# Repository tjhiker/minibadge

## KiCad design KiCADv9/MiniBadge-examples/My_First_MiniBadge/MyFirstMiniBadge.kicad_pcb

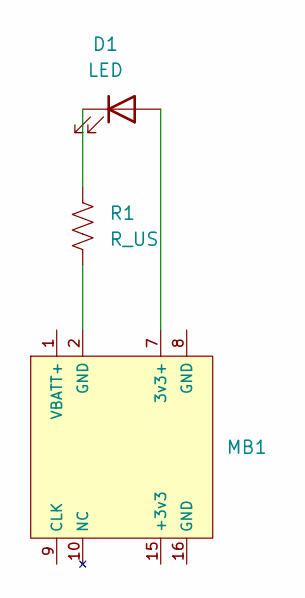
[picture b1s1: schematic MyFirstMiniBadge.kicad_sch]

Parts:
D1: LED; LED_1206_3216Metric_Pad1.42x1.75mm_HandSolder
MB1: MiniBadge_Simple_Edge_Curved
R1: R_US; R_1206_3216Metric_Pad1.30x1.75mm_HandSolder

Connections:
unnamed: D1.2 (A), MB1.7 (3v3+)
unnamed: D1.1 (K), R1.1
unnamed: MB1.2 (GND), R1.2

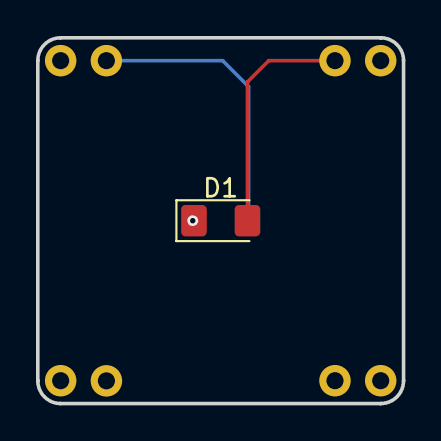
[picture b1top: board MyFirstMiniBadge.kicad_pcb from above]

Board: 2 copper layers, 20.3 x 20.3 mm, 3 parts (1 on the bottom side), 3 nets.

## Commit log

2025-03-26 KiCADv9 Addition
    Added multiple footprints
2025-03-26 Cleanup
